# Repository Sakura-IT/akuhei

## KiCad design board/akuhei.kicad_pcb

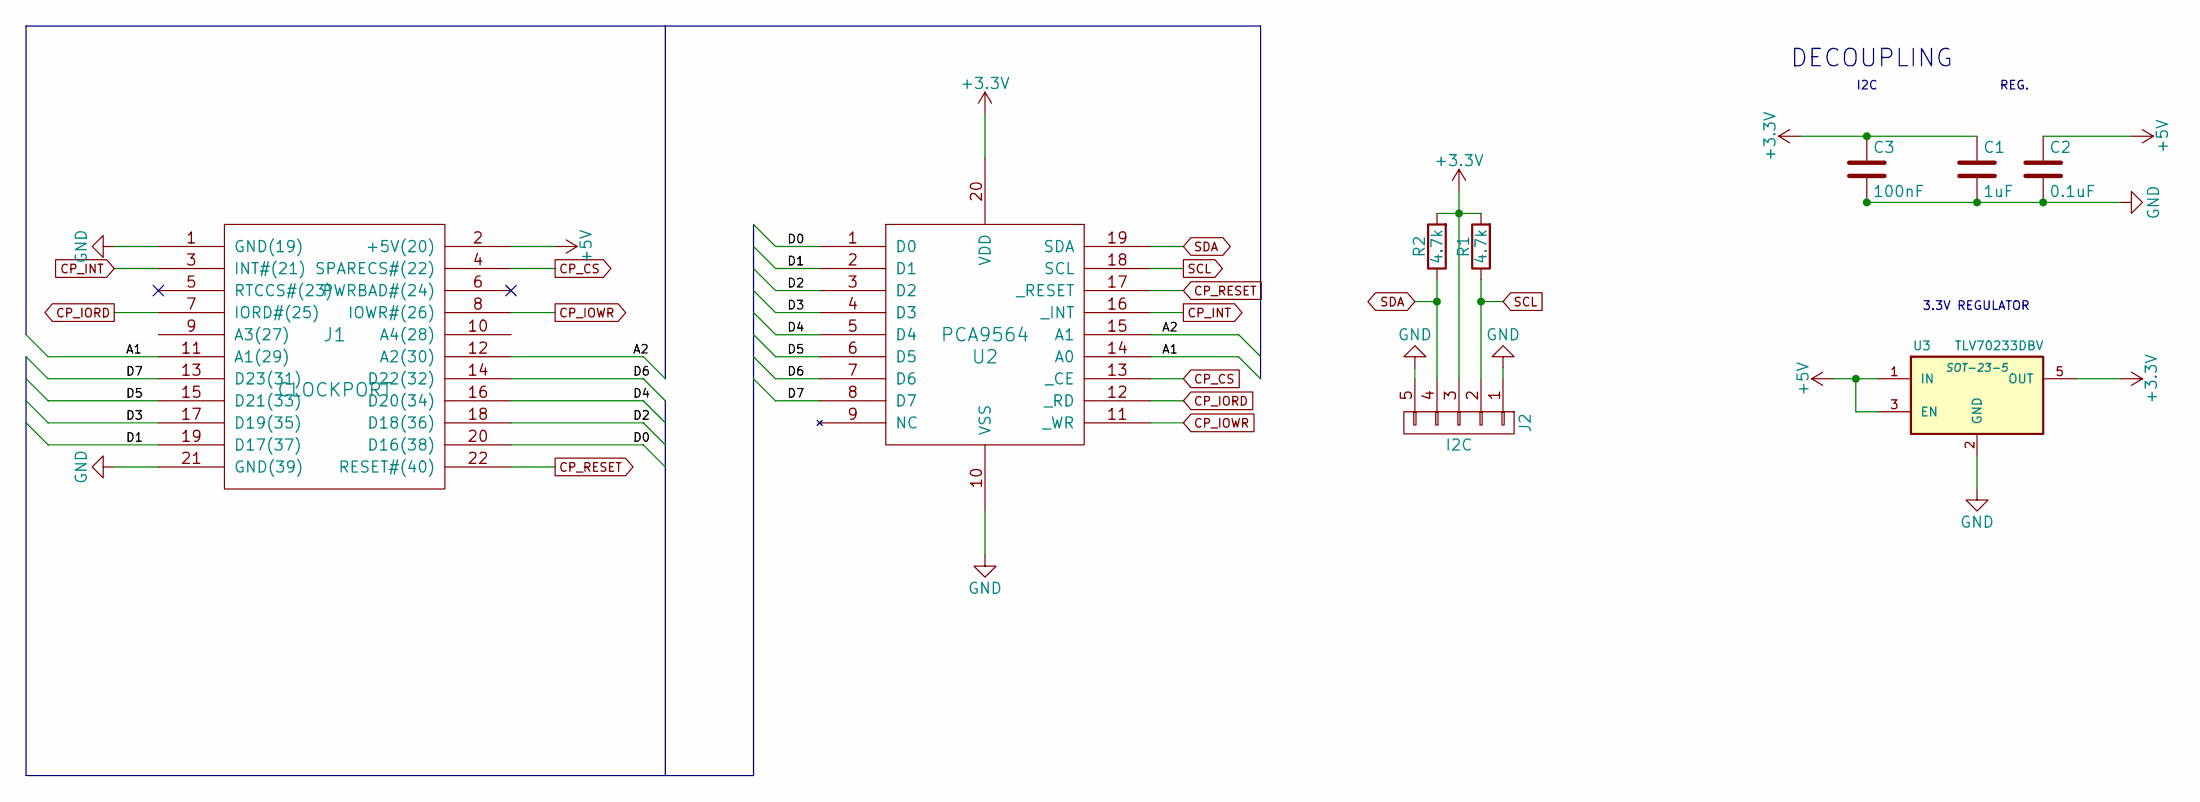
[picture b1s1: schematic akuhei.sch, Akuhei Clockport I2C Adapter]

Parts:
C1: 1uF; C_0603
C2: 0.1uF; C_0603
C3: 100nF; C_0603
J1: CLOCKPORT; 87758-2216
J2: I2C; Pin_Header_Angled_1x05
R1, R2: 4.7k; R_0603
U2: PCA9564; TSSOP-20_4.4x6.5mm_Pitch0.65mm
U3: TLV70233DBV; SOT-23-5

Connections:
+3V3: C1.1, C3.1, J2.3, R1.2, R2.2, U2.20 (VDD), U3.5 (OUT)
+5V: C2.1, J1.2 (+5V(20)), U3.1 (IN), U3.3 (EN)
/A1: J1.11 (A1(29)), U2.14 (A0)
/A2: J1.12 (A2(30)), U2.15 (A1)
/D0: J1.20 (D16(38)), U2.1 (D0)
/D1: J1.19 (D17(37)), U2.2 (D1)
/D2: J1.18 (D18(36)), U2.3 (D2)
/D3: J1.17 (D19(35)), U2.4 (D3)
/D4: J1.16 (D20(34)), U2.5 (D4)
/D5: J1.15 (D21(33)), U2.6 (D5)
/D6: J1.14 (D22(32)), U2.7 (D6)
/D7: J1.13 (D23(31)), U2.8 (D7)
CP_CS: J1.4 (SPARECS#(22)), U2.13 (_CE)
CP_INT: J1.3 (INT#(21)), U2.16 (_INT)
CP_IORD: J1.7 (IORD#(25)), U2.12 (_RD)
CP_IOWR: J1.8 (IOWR#(26)), U2.11 (_WR)
CP_RESET: J1.22 (RESET#(40)), U2.17 (_RESET)
GND: C1.2, C2.2, C3.2, J1.1 (GND(19)), J1.21 (GND(39)), J2.1, J2.5, U2.10 (VSS), U3.2 (GND)
SCL: J2.2, R1.1, U2.18 (SCL)
SDA: J2.4, R2.1, U2.19 (SDA)

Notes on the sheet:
3.3V REGULATOR
REG.
I2C
DECOUPLING

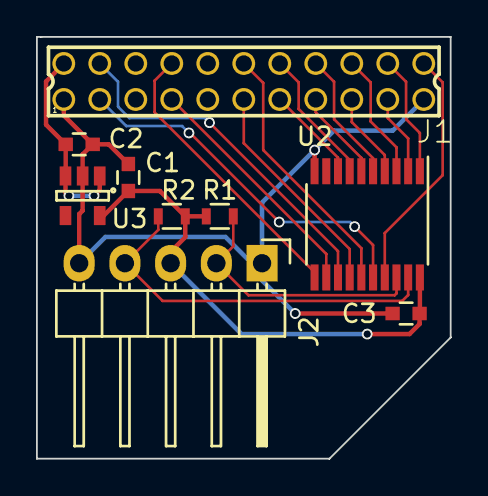
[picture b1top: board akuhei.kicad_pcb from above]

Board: 2 copper layers, 23.0 x 23.4 mm, 9 parts (0 on the bottom side), 20 nets.

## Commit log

2015-08-16 Add project.
2015-08-16 Finishing touches...
2015-08-19 Move vias out of pads.
2015-08-19 Add no-CPLD version.
2015-08-20 Ignore .bak files.
2015-08-20 Ignore bak files, not only .bak.
2015-12-12 Small changesof board
2015-12-14 removing error
